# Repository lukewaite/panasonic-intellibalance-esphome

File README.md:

# Panasonic Intelli-Balance 200 ↔ ESPHome

Home Assistant control of a **Panasonic Intelli-Balance 200 ERV**, in the spirit of ratgdo. A small
ESP32-C6 board sits inline on the 4-wire cable between the ERV and its FV-SW20VEC1 wall control and
runs ESPHome over Thread. The wall control keeps working as before.

What it does:

- **Shows** power, airflow, ASHRAE setting, boost, the ventilation rest cycle, and inside/outside
  temperature and humidity.
- **Controls** power, a 60 min boost, supply/exhaust airflow and the ASHRAE run time.
- **Turns the ERV back on after a power failure**, which the ERV doesn't do by itself.
- **Fails safe:** unpowered or crashed, the board passes the link straight through.

## Install

A device config only names the device and sets up its network; the package brings in the rest:

```yaml
substitutions:
  name: ervlink
  friendly_name: ERV link
packages:
  ervlink: github://lukewaite/panasonic-intellibalance-esphome/firmware/ervlink-package.yaml@main
esphome:
  name: ${name}
  friendly_name: ${friendly_name}
api:
  encryption:
    key: !secret ervlink_api_key
wifi:                       # or Thread: see firmware/ervlink.yaml
  ssid: !secret wifi_ssid
  password: !secret wifi_password
```

`@main` follows the latest release (ESPHome refreshes it daily, and `main` always loads the
core at its latest release tag). To stay on one version, use a tag instead: `@fw-v16`.

## What's here

| | |
|---|---|
| [`firmware/ervlink-package.yaml`](firmware/ervlink-package.yaml) | The ESPHome package: the whole board, pulled in by a short device config. |
| [`firmware/ervlink.yaml`](firmware/ervlink.yaml), [`example-wifi.yaml`](firmware/example-wifi.yaml) | Device configs for Thread or Wi-Fi. Paste one into the ESPHome Device Builder, set the name and secrets. |
| [`hardware/DESIGN.md`](hardware/DESIGN.md) | The board: how it works and why each part was chosen. |
| [`hardware/kicad/`](hardware/kicad/) | KiCad project (generated by the scripts in `gen/`), with a [schematic PDF](hardware/kicad/ervlink-schematic.pdf) and JLCPCB gerbers, BOM and placement in [`fab/`](hardware/kicad/fab/). |
| [`hardware/bom-digikey.csv`](hardware/bom-digikey.csv) | The hand-soldered parts, enclosure and standoffs. |
| [`hardware/STATUS.md`](hardware/STATUS.md) | Build notes and a bring-up checklist. |
| [`docs/firmware.md`](docs/firmware.md) | How the board takes over the link, and how it resumes after a power cut. |
| [`docs/protocol.md`](docs/protocol.md) | How the ERV and wall control talk, and how to decode a capture. |

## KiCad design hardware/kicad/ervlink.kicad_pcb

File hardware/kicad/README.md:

# KiCad project

Everything here is generated: edit the scripts in `gen/`, never the KiCad files.

```bash
cd gen
python3 gen_sch.py                       # schematic (ervlink.kicad_sch)
KPY=/Applications/KiCad/KiCad.app/Contents/Frameworks/Python.framework/Versions/3.9/bin/python3
$KPY gen_pcb.py                          # place, autoroute (Freerouting), pour
$KPY gen_pcb.py --silk-only              # change existing silkscreen text only
$KPY gen_fab.py                          # fab/: gerber zip, JLCPCB BOM + CPL
```

- **Freerouting isn't deterministic**: a full `gen_pcb.py` reroutes every track. For text
  changes use `--silk-only`, so the copper stays as ordered.
- Freerouting 2.4.1 is at `~/.local/share/freerouting/` and needs Java 25 (`mise.toml`).
  `kicad-cli` is at `/Applications/KiCad/KiCad.app/Contents/MacOS/kicad-cli`.
- `gen_fab.py` carries JLCPCB rotation/offset corrections (`CPL_ROT`, `CPL_OFFSET`) measured
  against their placement preview; re-check the preview after any footprint change.

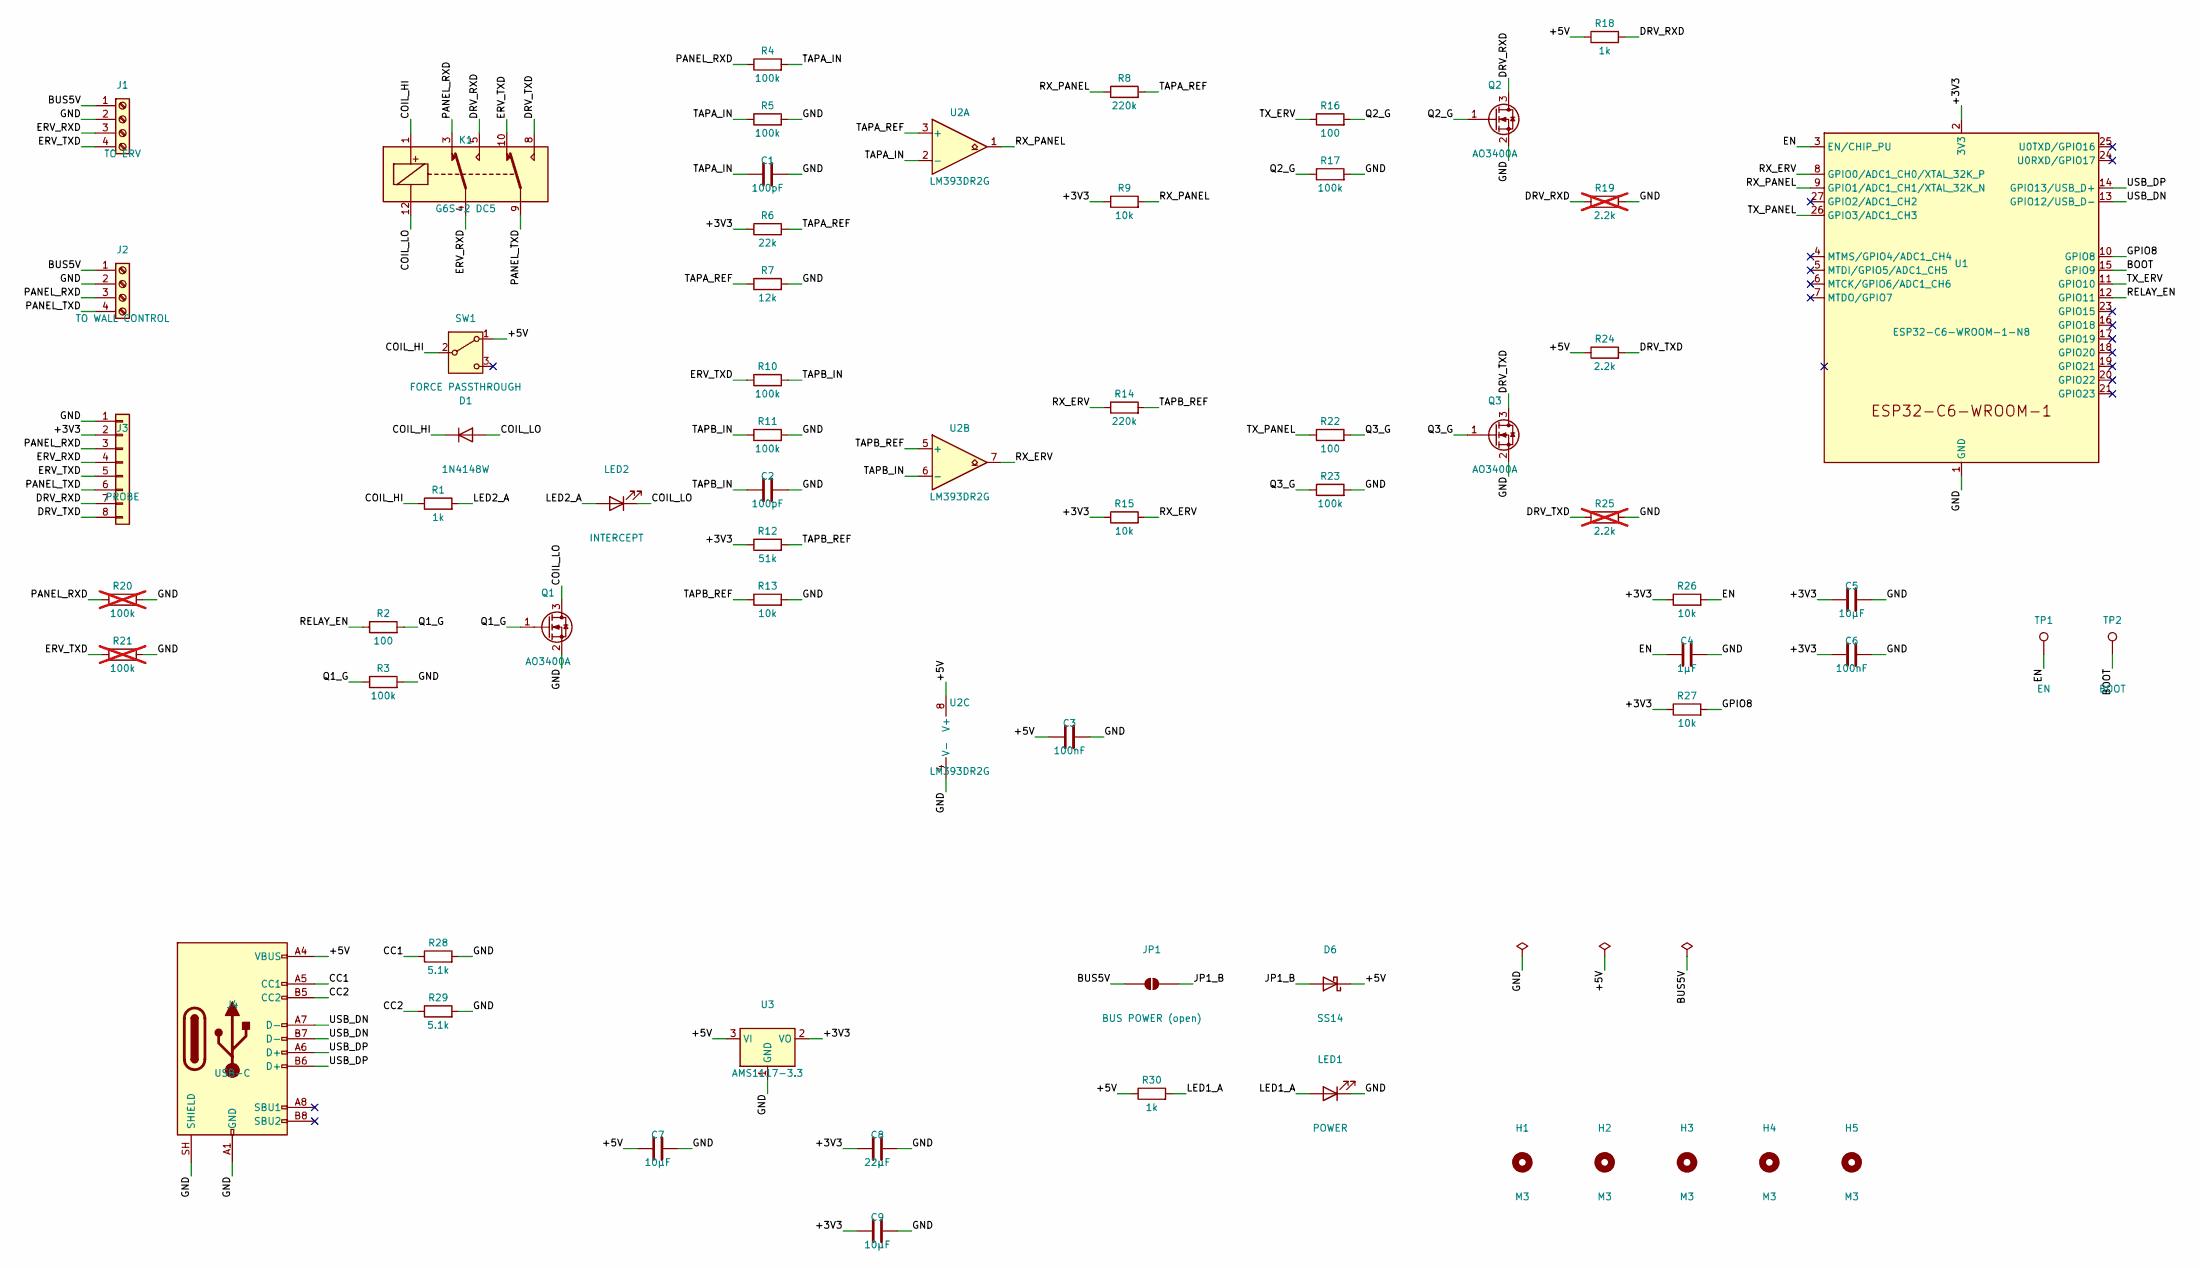
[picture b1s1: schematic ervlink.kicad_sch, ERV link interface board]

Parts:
C1, C2: 100pF; C_0805_2012Metric; LCSC C1790
C3, C6: 100nF; C_0805_2012Metric; LCSC C49678
C4: 1µF; C_0805_2012Metric; LCSC C28323
C5, C7, C9: 10µF; C_0805_2012Metric; LCSC C15850
C8: 22µF; C_0805_2012Metric; LCSC C45783
D1: 1N4148W; D_SOD-123; LCSC C81598
D6: SS14; D_SMA; LCSC C2480
H1, H2, H3, H4, H5: M3; MountingHole_3.2mm_M3
J1: TO ERV; TerminalBlock_Phoenix_MKDS-1,5-4-5.08_1x04_P5.08mm_Horizont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
J2: TO WALL CONTROL; TerminalBlock_Phoenix_MKDS-1,5-4-5.08_1x04_P5.08mm_Horizont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
J3: PROBE; PinHeader_1x08_P2.54mm_Vertical
J4: USB-C; USB_C_Receptacle_HRO_TYPE-C-31-M-12; LCSC C165948
JP1: BUS POWER (open); SolderJumper-2_P1.3mm_Open_RoundedPad1.0x1.5mm
K1: G6S-2 DC5; Relay_DPDT_Omron_G6S-2
LED1: POWER; LED_0805_2012Metric; LCSC C2297
LED2: INTERCEPT; LED_0805_2012Metric; LCSC C2296
Q1, Q2, Q3: AO3400A; SOT-23; LCSC C20917
R1, R18, R30: 1k; R_0805_2012Metric; LCSC C17513
R2, R16, R22: 100; R_0805_2012Metric; LCSC C17408
R3, R4, R5, R10, R11, R17, R23: 100k; R_0805_2012Metric; LCSC C149504
R6: 22k; R_0805_2012Metric; LCSC C17560
R7: 12k; R_0805_2012Metric; LCSC C17444
R8, R14: 220k; R_0805_2012Metric; LCSC C17556
R9, R13, R15, R26, R27: 10k; R_0805_2012Metric; LCSC C17414
R12: 51k; R_0805_2012Metric; LCSC C17737
R19, R25: 2.2k; R_0805_2012Metric; not fitted
R20, R21: 100k; R_0805_2012Metric; not fitted
R24: 2.2k; R_0805_2012Metric; LCSC C17520
R28, R29: 5.1k; R_0805_2012Metric; LCSC C27834
SW1: FORCE PASSTHROUGH; SW_Slide_SPDT_Straight_CK_OS102011MS2Q
TP1: EN; TestPoint_Pad_D1.5mm
TP2: BOOT; TestPoint_Pad_D1.5mm
U1: ESP32-C6-WROOM-1-N8; ESP32-C6-WROOM-1; LCSC C5366877
U2: LM393DR2G; SOIC-8_3.9x4.9mm_P1.27mm; LCSC C7955
U3: AMS1117-3.3; SOT-223-3_TabPin2; LCSC C6186

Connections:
/+3V3: C5.1, C6.1, C8.1, C9.1, J3.2, R6.1, R9.1, R12.1, R15.1, R26.1, R27.1, U1.2 (3V3), U3.2 (VO)
/+5V: C3.1, C7.1, D6.1 (K), J4.A4 (VBUS), J4.A9 (VBUS), J4.B4 (VBUS), J4.B9 (VBUS), R18.1, R24.1, R30.1, SW1.1 (A), U2.8 (V+), U3.3 (VI)
/BOOT: TP2.1, U1.15 (GPIO9)
/BUS5V: J1.1, J2.1, JP1.1 (A)
/CC1: J4.A5 (CC1), R28.1
/CC2: J4.B5 (CC2), R29.1
/COIL_HI: D1.1 (K), K1.1, R1.1, SW1.2 (B)
/COIL_LO: D1.2 (A), K1.12, LED2.1 (K), Q1.3 (D)
/DRV_RXD: J3.7, K1.5, Q2.3 (D), R18.2, R19.1
/DRV_TXD: J3.8, K1.8, Q3.3 (D), R24.2, R25.1
/EN: C4.1, R26.2, TP1.1, U1.3 (EN/CHIP_PU)
/ERV_RXD: J1.3, J3.4, K1.4
/ERV_TXD: J1.4, J3.5, K1.10, R10.1, R21.1
/GND: C1.2, C2.2, C3.2, C4.2, C5.2, C6.2, C7.2, C8.2, C9.2, J1.2, J2.2, J3.1, J4.A1 (GND), J4.A12 (GND), J4.B1 (GND), J4.B12 (GND), J4.SH (SHIELD), LED1.1 (K), Q1.2 (S), Q2.2 (S), Q3.2 (S), R3.2, R5.2, R7.2, R11.2, R13.2, R17.2, R19.2, R20.2, R21.2, R23.2, R25.2, R28.2, R29.2, U1.1 (GND), U1.28 (GND), U1.29 (GND), U2.4 (V-), U3.1 (GND)
/GPIO8: R27.2, U1.10 (GPIO8)
/JP1_B: D6.2 (A), JP1.2 (B)
/LED1_A: LED1.2 (A), R30.2
/LED2_A: LED2.2 (A), R1.2
/PANEL_RXD: J2.3, J3.3, K1.3, R4.1, R20.1
/PANEL_TXD: J2.4, J3.6, K1.9
/Q1_G: Q1.1 (G), R2.2, R3.1
/Q2_G: Q2.1 (G), R16.2, R17.1
/Q3_G: Q3.1 (G), R22.2, R23.1
/RELAY_EN: R2.1, U1.12 (GPIO11)
/RX_ERV: R14.1, R15.2, U1.8 (GPIO0/ADC1_CH0/XTAL_32K_P), U2.7
/RX_PANEL: R8.1, R9.2, U1.9 (GPIO1/ADC1_CH1/XTAL_32K_N), U2.1
/TAPA_IN: C1.1, R4.2, R5.1, U2.2 (-)
/TAPA_REF: R6.2, R7.1, R8.2, U2.3 (+)
/TAPB_IN: C2.1, R10.2, R11.1, U2.6 (-)
/TAPB_REF: R12.2, R13.1, R14.2, U2.5 (+)
/TX_ERV: R16.1, U1.11 (GPIO10)
/TX_PANEL: R22.1, U1.26 (GPIO3/ADC1_CH3)
/USB_DN: J4.A7 (D-), J4.B7 (D-), U1.13 (GPIO12/USB_D-)
/USB_DP: J4.A6 (D+), J4.B6 (D+), U1.14 (GPIO13/USB_D+)

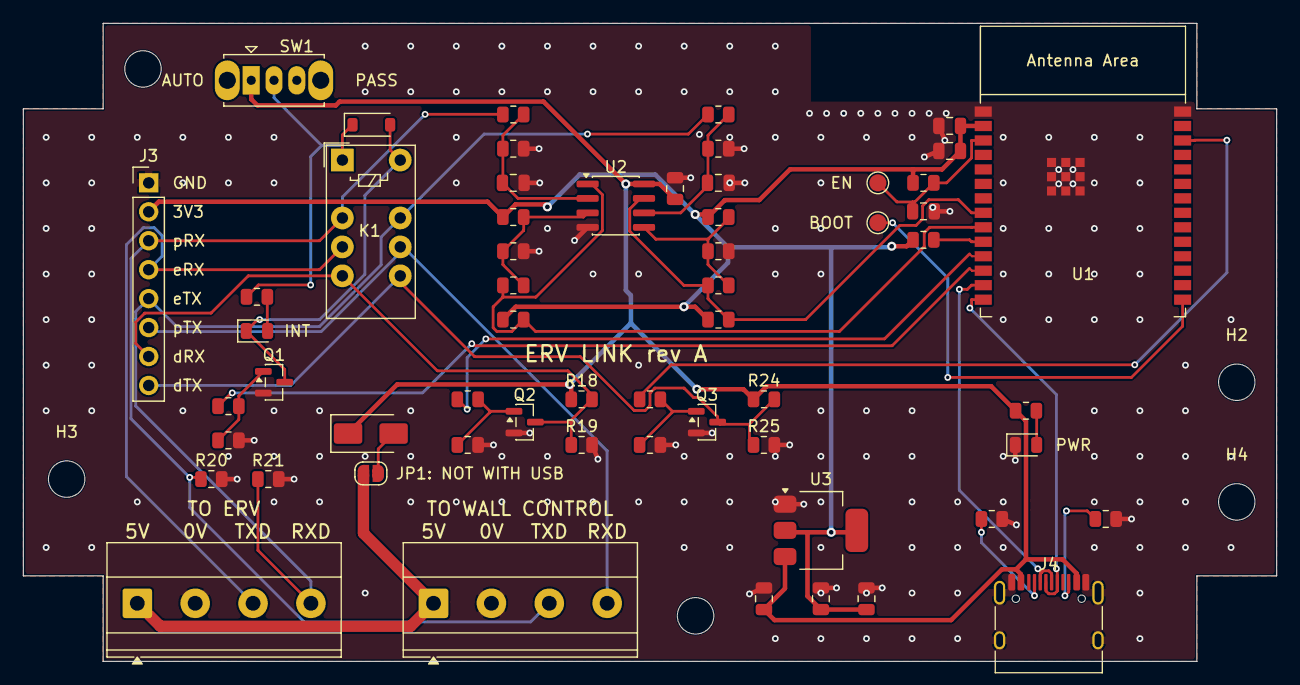
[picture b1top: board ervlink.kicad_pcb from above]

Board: 2 copper layers, 110.0 x 56.0 mm, 63 parts (0 on the bottom side), 34 nets.

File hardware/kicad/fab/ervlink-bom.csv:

Comment,Designator,Footprint,LCSC Part #
100k,"R3,R4,R5,R10,R11,R17,R23",R_0805_2012Metric,C149504
10µF,"C5,C7,C9",C_0805_2012Metric,C15850
USB-C,J4,USB_C_Receptacle_HRO_TYPE-C-31-M-12,C165948
100,"R2,R16,R22",R_0805_2012Metric,C17408
10k,"R9,R13,R15,R26,R27",R_0805_2012Metric,C17414
12k,R7,R_0805_2012Metric,C17444
1k,"R1,R18,R30",R_0805_2012Metric,C17513
2.2k,R24,R_0805_2012Metric,C17520
220k,"R8,R14",R_0805_2012Metric,C17556
22k,R6,R_0805_2012Metric,C17560
51k,R12,R_0805_2012Metric,C17737
100pF,"C1,C2",C_0805_2012Metric,C1790
AO3400A,"Q1,Q2,Q3",SOT-23,C20917
INTERCEPT,LED2,LED_0805_2012Metric,C2296
POWER,LED1,LED_0805_2012Metric,C2297
SS14,D6,D_SMA,C2480
5.1k,"R28,R29",R_0805_2012Metric,C27834
1µF,C4,C_0805_2012Metric,C28323
22µF,C8,C_0805_2012Metric,C45783
100nF,"C3,C6",C_0805_2012Metric,C49678
ESP32-C6-WROOM-1-N8,U1,ESP32-C6-WROOM-1,C5366877
AMS1117-3.3,U3,SOT-223-3_TabPin2,C6186
LM393DR2G,U2,SOIC-8_3.9x4.9mm_P1.27mm,C7955
1N4148W,D1,D_SOD-123,C81598

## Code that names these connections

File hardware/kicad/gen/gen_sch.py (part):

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     (370, 80),
     {"1": "GND", "28": "GND", "29": "GND", "2": "+3V3", "3": "EN",
      # Footprint pins 1-14 are the module's left column (toward the comparators).
      # Gate-driving pins have no pull-up at reset: GPIO10, GPIO11, GPIO3.
      "9": "RX_PANEL",    # GPIO1,  UART1 RX (left)
      "11": "TX_ERV",     # GPIO10, UART1 TX (left, no pull at reset)
      "8": "RX_ERV",      # GPIO0,  UART0 RX (left)
      "26": "TX_PANEL",   # GPIO3,  UART0 TX (right, no pull at reset)
      "12": "RELAY_EN",   # GPIO11 (left, no pull at reset)
      "13": "USB_DN", "14": "USB_DP",
      "15": "BOOT",       # GPIO9 strap
      "10": "GPIO8",      # GPIO8 strap, pulled high
      "4": None, "5": None, "6": None, "7": None, "16": None, "17": None, "18": None,
      "19": None, "20": None, "21": None, "22": None, "23": None, "24": None, "25": None,
      "27": None},
     lcsc="C5366877")
R("R26", "10k", "+3V3", "EN", (320, 135), note="EN pull-up")
C("C4", "1u", "EN", "GND", (320, 145))
R("R27", "10k", "+3V3", "GPIO8", (320, 155), note="GPIO8 strap high")
part("TP1", "Connector:TestPoint", "EN", "TestPoint:TestPoint_Pad_D1.5mm", (385, 145),
     {"1": "EN"}, note="short to GND to reset")
part("TP2", "Connector:TestPoint", "BOOT", "TestPoint:TestPoint_Pad_D1.5mm", (400, 145),
     {"1": "BOOT"}, note="GPIO9; short to GND at reset for ROM download mode")
C("C5", "10u", "+3V3", "GND", (350, 135))
C("C6", "100n", "+3V3", "GND", (350, 145))

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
